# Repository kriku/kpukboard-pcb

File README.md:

# kpukboard-pcb
Bluetooth keyboard - printed circuit board design

kpukboard is a 38 key column-staggered choc split keyboard

it meant to be used with a [seeeduino xiao ble](https://wiki.seeedstudio.com/XIAO_BLE/)

as thin as possible with kailh choc mini switches

BOM:
- kailh choc switch mini - 38 pcs
- kailh choc keycap - 38 pcs
- seeeduino xiao ble - 2 pcs
- sod-123 diodes - 38 pcs
- pcb-7 welding terminals m3 - 4 pcs 
- m3 screw 6mm - 4 pcs
- battery 603030 - 2 pcs
- mss-22d18 power switches - 2 pcs
- silicone rubber pad 1mm - 2 pcs

[build process (telegram channel)](https://t.me/kpukboard)

inspired by [TOTEM](https://github.com/GEIGEIGEIST/TOTEM)

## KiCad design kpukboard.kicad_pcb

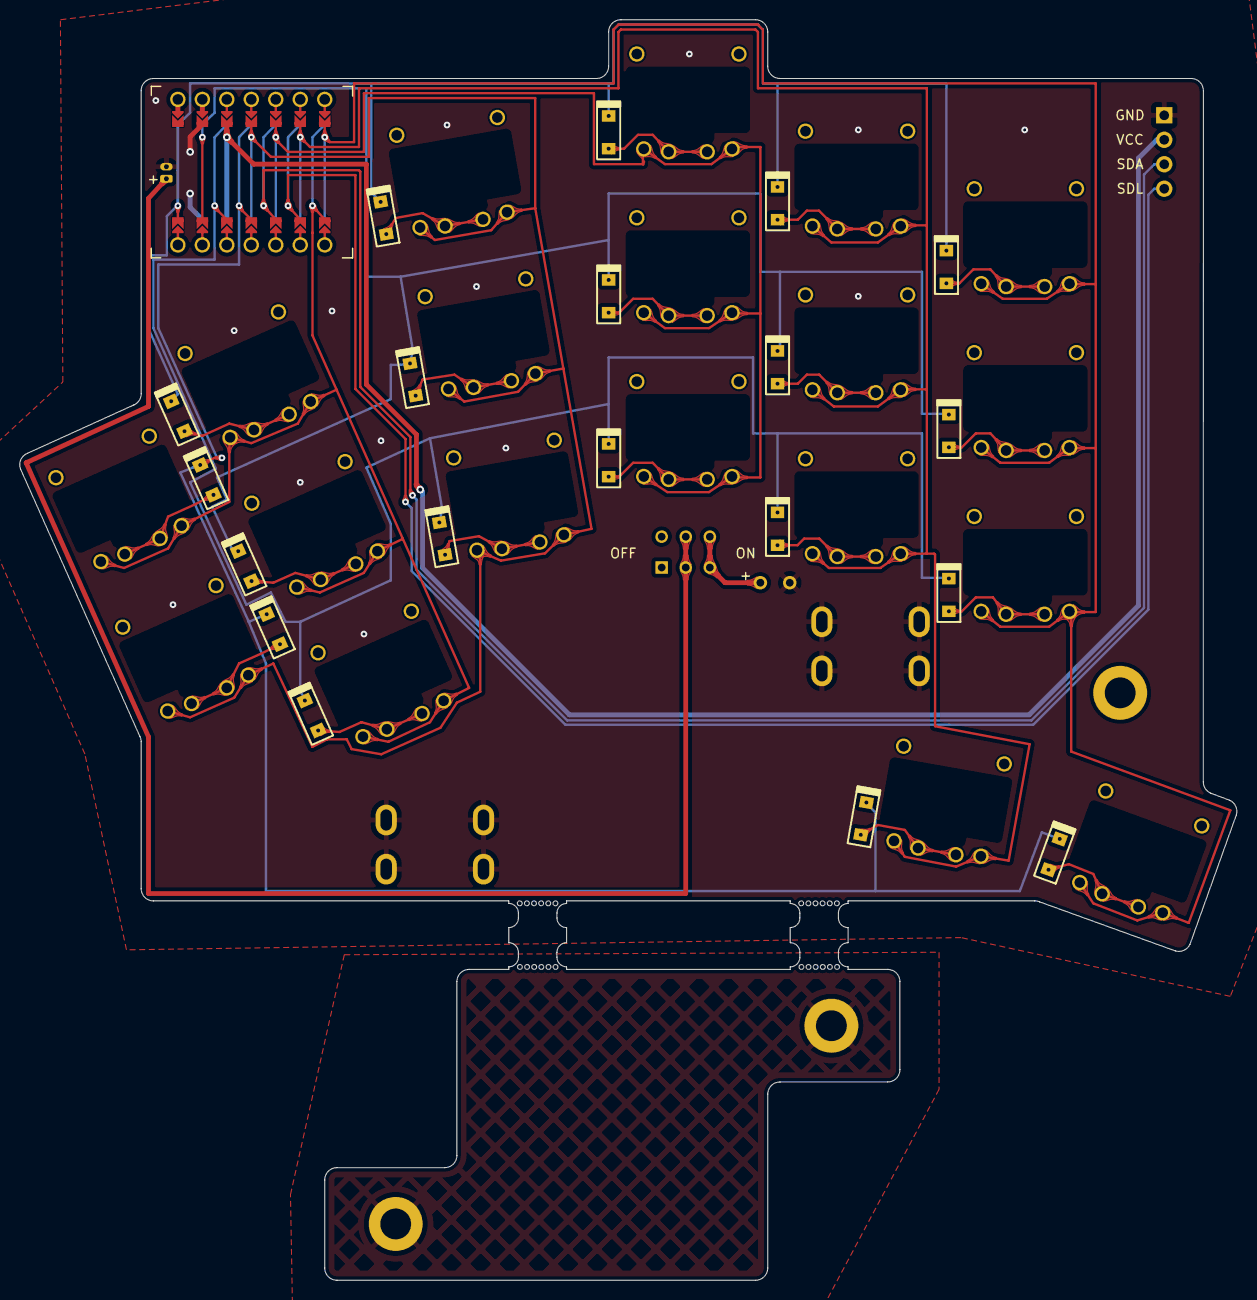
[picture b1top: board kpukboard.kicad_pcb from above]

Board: 2 copper layers, 126.3 x 130.8 mm, 48 parts (0 on the bottom side), 34 nets.

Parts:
D1, D2, D3, D4, D5, D6, D7, D8, D9, D10, D11, D12, D13, D14, D15, D16, D17, D18, D19: D_Small; Diode_SOD123_THT_2
H1, H2: MountingHole_Pad; pcb7xm3
H3, H4, H5: MountingHole_Pad; MountingHole_3.2mm_M3_DIN965_Pad
J1: Conn_01x02_Female; battery-pad
J2: Conn_01x02_Female; Molex_PicoBlade_53048-0210_1x02_P1.25mm_Horizontal
J3: Conn_01x04_Male; PinHeader_1x04_P2.54mm_Vertical
PSW1: SW_SPDT; SW_MS-22D18G2ROHS
SW1, SW2, SW3, SW4, SW5, SW6, SW7, SW8, SW9, SW10, SW11, SW12, SW13, SW14, SW15, SW16, SW17, SW18, SW19: SW_Push_45deg; Kailh_PG1232_reversible
U1: xiao-ble; Xiao THT jumper pad

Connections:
BAT+: J2.1, PSW1.2 (B)
GND: H1.1, H2.1, H3.1, H4.1, J1.2, J2.2, J3.1, U1.13 (GND)
unnamed: D1.2 (A), SW1.2
unnamed: D2.2 (A), SW2.2
unnamed: D3.2 (A), SW3.2
unnamed: D4.2 (A), SW4.2
unnamed: D5.2 (A), SW5.2
unnamed: D6.2 (A), SW6.2
unnamed: D7.2 (A), SW7.2
unnamed: D8.2 (A), SW8.2
unnamed: D9.2 (A), SW9.2
unnamed: D10.2 (A), SW10.2
unnamed: D11.2 (A), SW11.2
unnamed: D12.2 (A), SW12.2
unnamed: D13.2 (A), SW13.2
unnamed: D14.2 (A), SW14.2
unnamed: D15.2 (A), SW15.2
unnamed: D16.2 (A), SW16.2
unnamed: D17.2 (A), SW17.2
unnamed: D18.2 (A), SW18.2
unnamed: D19.2 (A), SW19.2
VBAT: J1.1, PSW1.3 (C)
VCC: J3.2, U1.12 (3V3)
col0: SW1.1, SW6.1, SW11.1, SW16.1, U1.7 (B8_TX/1.11)
col1: SW2.1, SW7.1, SW12.1, SW17.1, U1.11 (A6_MOSI/1.15)
col2: SW3.1, SW8.1, SW13.1, U1.10 (A5_MISO/1.14)
col3: SW4.1, SW9.1, SW14.1, SW18.1, U1.9 (A7_SCK/1.13)
col4: SW5.1, SW10.1, SW15.1, SW19.1, U1.8 (B9_RX/1.12)
row0: D1.1 (K), D2.1 (K), D3.1 (K), D4.1 (K), D5.1 (K), U1.1 (A2/0.02_H)
row1: D6.1 (K), D7.1 (K), D8.1 (K), D9.1 (K), D10.1 (K), U1.2 (A4/0.03_H)
row2: D11.1 (K), D12.1 (K), D13.1 (K), D14.1 (K), D15.1 (K), U1.3 (A10/0.28)
row3: D16.1 (K), D17.1 (K), D18.1 (K), D19.1 (K), U1.4 (A11/0.29)
sda: J3.3, U1.5 (A8_SDA/0.04_H)
sdl: J3.4, U1.6 (A9_SCL/0.05_H)

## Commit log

2023-04-13 Init with last version of pcb design
2023-08-08 docs(build-process): WIP
